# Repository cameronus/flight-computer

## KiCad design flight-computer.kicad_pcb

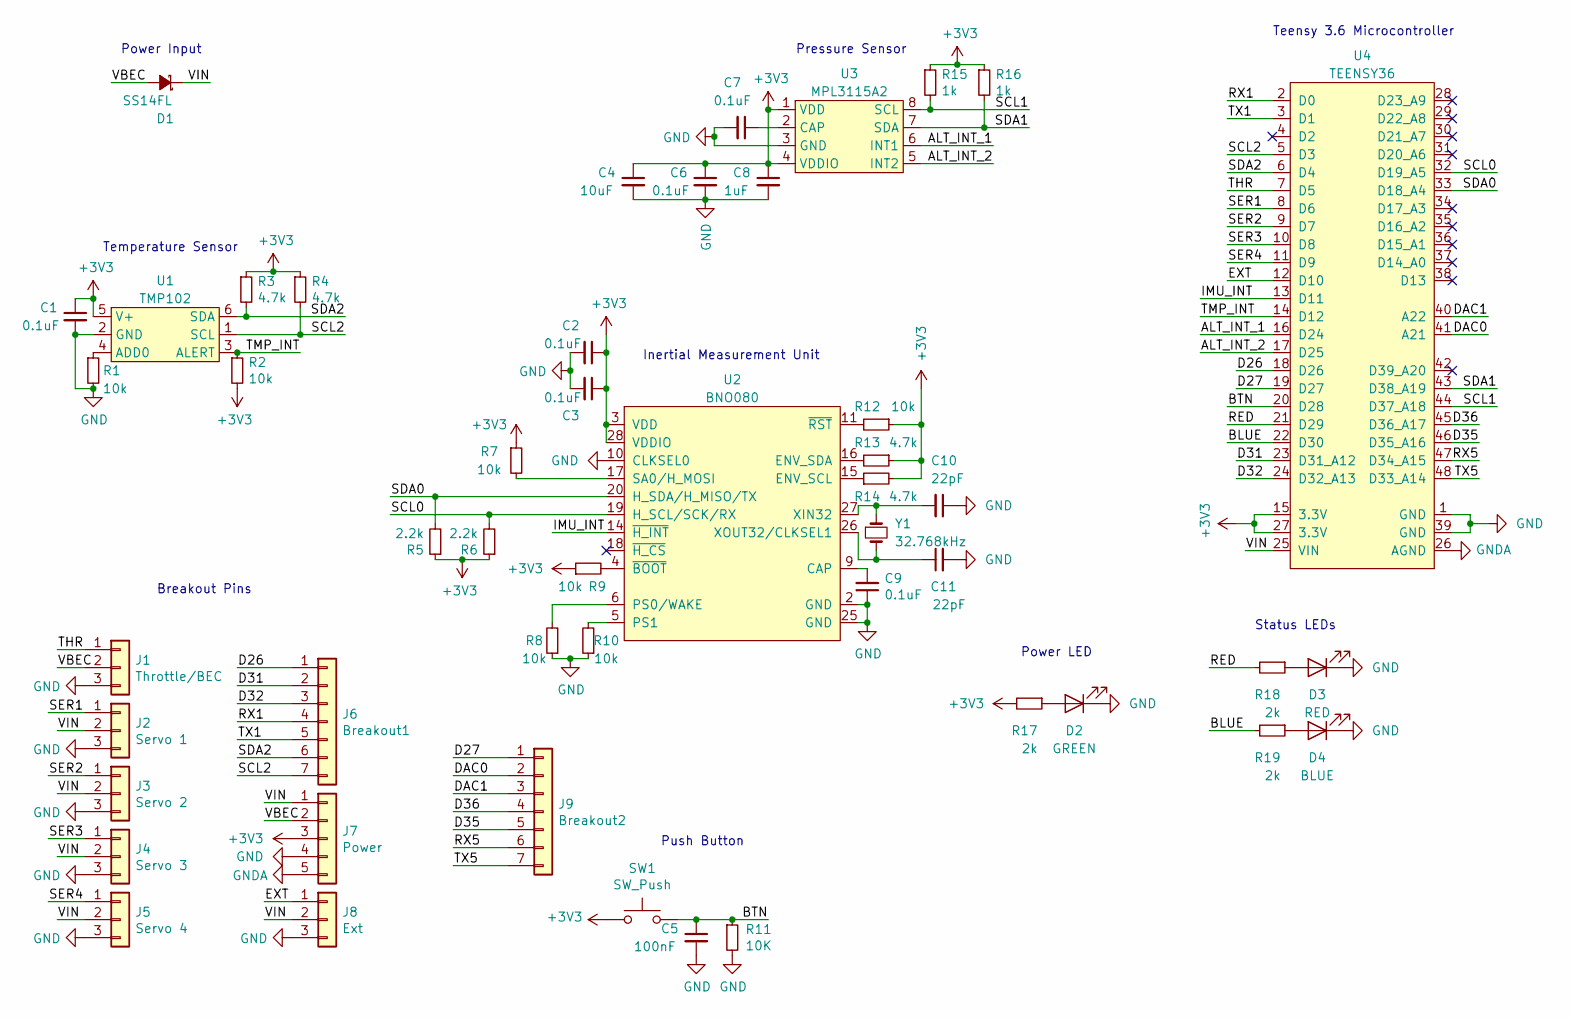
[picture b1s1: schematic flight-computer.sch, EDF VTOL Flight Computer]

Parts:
C1, C2, C3, C6, C7, C9: 0.1uF; C_0402_1005Metric
C4: 10uF; C_1206_3216Metric
C5: 100nF; C_0402_1005Metric
C8: 1uF; C_0402_1005Metric
C10, C11: 22pF; C_0402_1005Metric
D1: SS14FL; D_SOD-123F
D2: GREEN; LED_0603_1608Metric
D3: RED; LED_0603_1608Metric
D4: BLUE; LED_0603_1608Metric
J1: Throttle/BEC; PinHeader_1x03_P2.54mm_Vertical
J2: Servo 1; PinHeader_1x03_P2.54mm_Vertical
J3: Servo 2; PinHeader_1x03_P2.54mm_Vertical
J4: Servo 3; PinHeader_1x03_P2.54mm_Vertical
J5: Servo 4; PinHeader_1x03_P2.54mm_Vertical
J6: Breakout1; PinHeader_1x07_P2.54mm_Vertical
J7: Power; PinHeader_1x05_P2.54mm_Vertical
J8: Ext; PinHeader_1x03_P2.54mm_Vertical
J9: Breakout2; PinHeader_1x07_P2.54mm_Vertical
R1, R2, R7, R8, R9, R10, R12: 10k; R_0402_1005Metric
R3, R4, R13, R14: 4.7k; R_0402_1005Metric
R5, R6: 2.2k; R_0402_1005Metric
R11: 10K; R_0402_1005Metric
R15, R16: 1k; R_0402_1005Metric
R17, R18, R19: 2k; R_0402_1005Metric
SW1: SW_Push; SW_SPST_PTS810
U1: TMP102; SOT-563; MPN TMP102AIDRLR
U2: BNO080; LGA-28_5.2x3.8mm_P0.5mm; MPN BNO080
U3: MPL3115A2; LGA-8_3x5mm_P1.25mm; MPN MPL3115A2
U4: TEENSY36
Y1: 32.768kHz; ABS07; MPN ABS07-32.768KHZ-1-T

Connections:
+3V3: C1.1, C2.1, C3.1, C4.1, C6.1, C8.1, J7.3, R2.2, R3.1, R4.1, R5.1, R6.1, R7.1, R9.1, R12.1, R13.1, R14.2, R15.1, R16.1, R17.2, SW1.1, U1.5 (V+), U2.3 (VDD), U2.28 (VDDIO), U3.1 (VDD), U3.4 (VDDIO), U4.15 (3.3V), U4.27 (3.3V)
/ALT_INT_1: U3.6 (INT1), U4.16 (D24)
/ALT_INT_2: U3.5 (INT2), U4.17 (D25)
/BLUE: R19.2, U4.22 (D30)
/BTN: C5.1, R11.1, SW1.2, U4.20 (D28)
/D26: J6.1, U4.18 (D26)
/D27: J9.1, U4.19 (D27)
/D31: J6.2, U4.23 (D31_A12)
/D32: J6.3, U4.24 (D32_A13)
/D35: J9.5, U4.46 (D35_A16)
/D36: J9.4, U4.45 (D36_A17)
/DAC0: J9.2, U4.41 (A21)
/DAC1: J9.3, U4.40 (A22)
/EXT: J8.1, U4.12 (D10)
/IMU_INT: U2.14 (~H_INT), U4.13 (D11)
/RED: R18.2, U4.21 (D29)
/RX1: J6.4, U4.2 (D0)
/RX5: J9.6, U4.47 (D34_A15)
/SCL0: R6.2, U2.19 (H_SCL/SCK/RX), U4.32 (D19_A5)
/SCL1: R15.2, U3.8 (SCL), U4.44 (D37_A18)
/SCL2: J6.7, R4.2, U1.1 (SCL), U4.5 (D3)
/SDA0: R5.2, U2.20 (H_SDA/H_MISO/TX), U4.33 (D18_A4)
/SDA1: R16.2, U3.7 (SDA), U4.43 (D38_A19)
/SDA2: J6.6, R3.2, U1.6 (SDA), U4.6 (D4)
/SER1: J2.1, U4.8 (D6)
/SER2: J3.1, U4.9 (D7)
/SER3: J4.1, U4.10 (D8)
/SER4: J5.1, U4.11 (D9)
/THR: J1.1, U4.7 (D5)
/TMP_INT: R2.1, U1.3 (ALERT), U4.14 (D12)
/TX1: J6.5, U4.3 (D1)
/TX5: J9.7, U4.48 (D33_A14)
/VBEC: D1.2 (A), J1.2, J7.2
/VIN: D1.1 (K), J2.2, J3.2, J4.2, J5.2, J7.1, J8.2, U4.25 (VIN)
GND: C1.2, C2.2, C3.2, C4.2, C5.2, C6.2, C7.2, C8.2, C9.1, C10.1, C11.2, D2.1 (K), D3.1 (K), D4.1 (K), J1.3, J2.3, J3.3, J4.3, J5.3, J7.4, J8.3, R1.2, R8.1, R10.1, R11.2, U1.2 (GND), U2.2 (GND), U2.10 (CLKSEL0), U2.25 (GND), U3.3 (GND), U4.1 (GND), U4.39 (GND)
GNDA: J7.5, U4.26 (AGND)
unnamed: C7.1, U3.2 (CAP)
unnamed: C9.2, U2.9 (CAP)
unnamed: C10.2, U2.27 (XIN32), Y1.1
unnamed: C11.1, U2.26 (XOUT32/CLKSEL1), Y1.2
unnamed: D2.2 (A), R17.1
unnamed: D3.2 (A), R18.1
unnamed: D4.2 (A), R19.1
unnamed: R1.1, U1.4 (ADD0)
unnamed: R7.2, U2.17 (SA0/H_MOSI)
unnamed: R8.2, U2.6 (PS0/WAKE)
unnamed: R9.2, U2.4 (~BOOT)
unnamed: R10.2, U2.5 (PS1)
unnamed: R12.2, U2.11 (~RST)
unnamed: R13.2, U2.16 (ENV_SDA)
unnamed: R14.1, U2.15 (ENV_SCL)

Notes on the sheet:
Temperature Sensor
Teensy 3.6 Microcontroller
Power Input
Pressure Sensor
Status LEDs
Breakout Pins
Inertial Measurement Unit
Push Button
Power LED

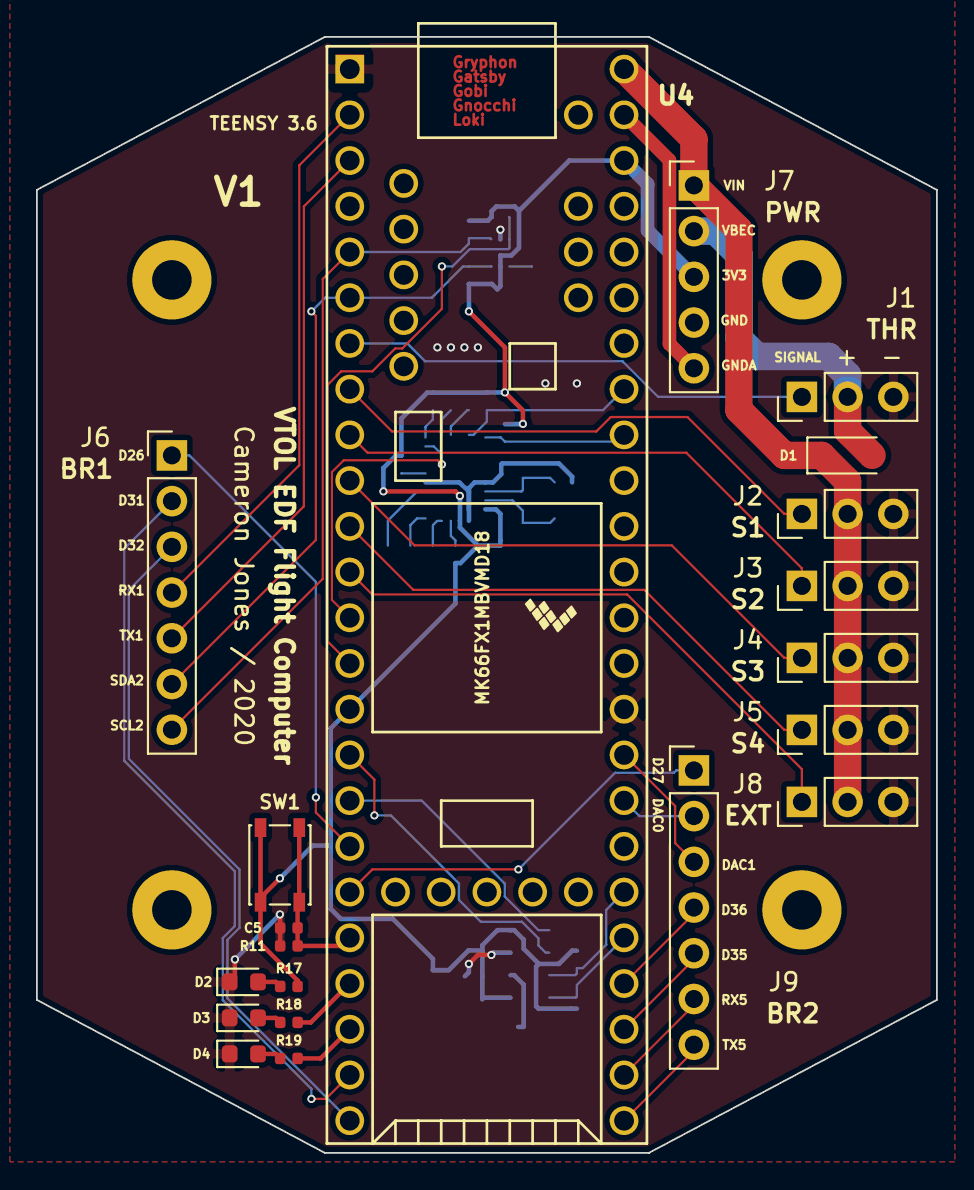
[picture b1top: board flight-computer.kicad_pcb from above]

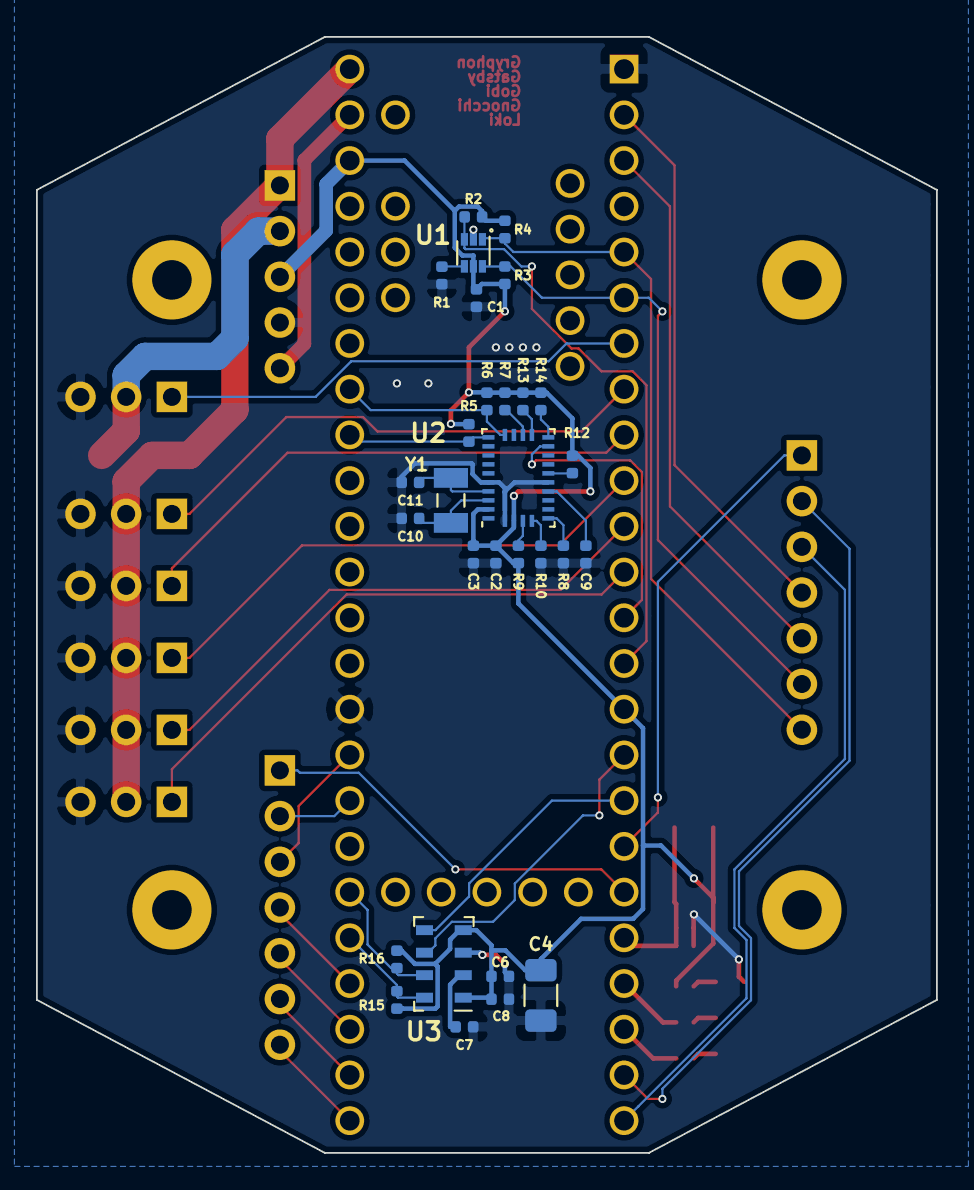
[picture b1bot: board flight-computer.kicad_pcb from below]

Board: 2 copper layers, 50.0 x 62.0 mm, 53 parts (29 on the bottom side), 51 nets.

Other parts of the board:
MH1, MH2, MH3, MH4: MountingHole_2.2mm_M2_Pad

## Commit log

2020-02-21 Progress on pinouts and STM32L433
2020-02-24 Teensy switched out as microcontroller
2020-02-24 Finished layout and annotation
2020-02-24 Assigning footprints
2020-02-24 Created custom footprint library
2020-02-24 New teensy footprint
2020-02-25 Laying out PCB
2020-02-25 Board outline
2020-02-25 Added holes
2020-02-25 New crystal footprint, layout changes
2020-02-25 Routing
2020-02-25 Finished routing
2020-02-25 Fixed C4 footprint
2020-02-25 Revamped routing
2020-02-26 Added mounting hole pads
2020-02-26 Re-routed a few traces
2020-02-26 Improved top silkscreen
2020-02-26 Cleaned up bottom silkscreen
2020-02-26 Easter egg
2020-02-26 Version number and mounting hole reference designators
2020-02-26 Version 1
